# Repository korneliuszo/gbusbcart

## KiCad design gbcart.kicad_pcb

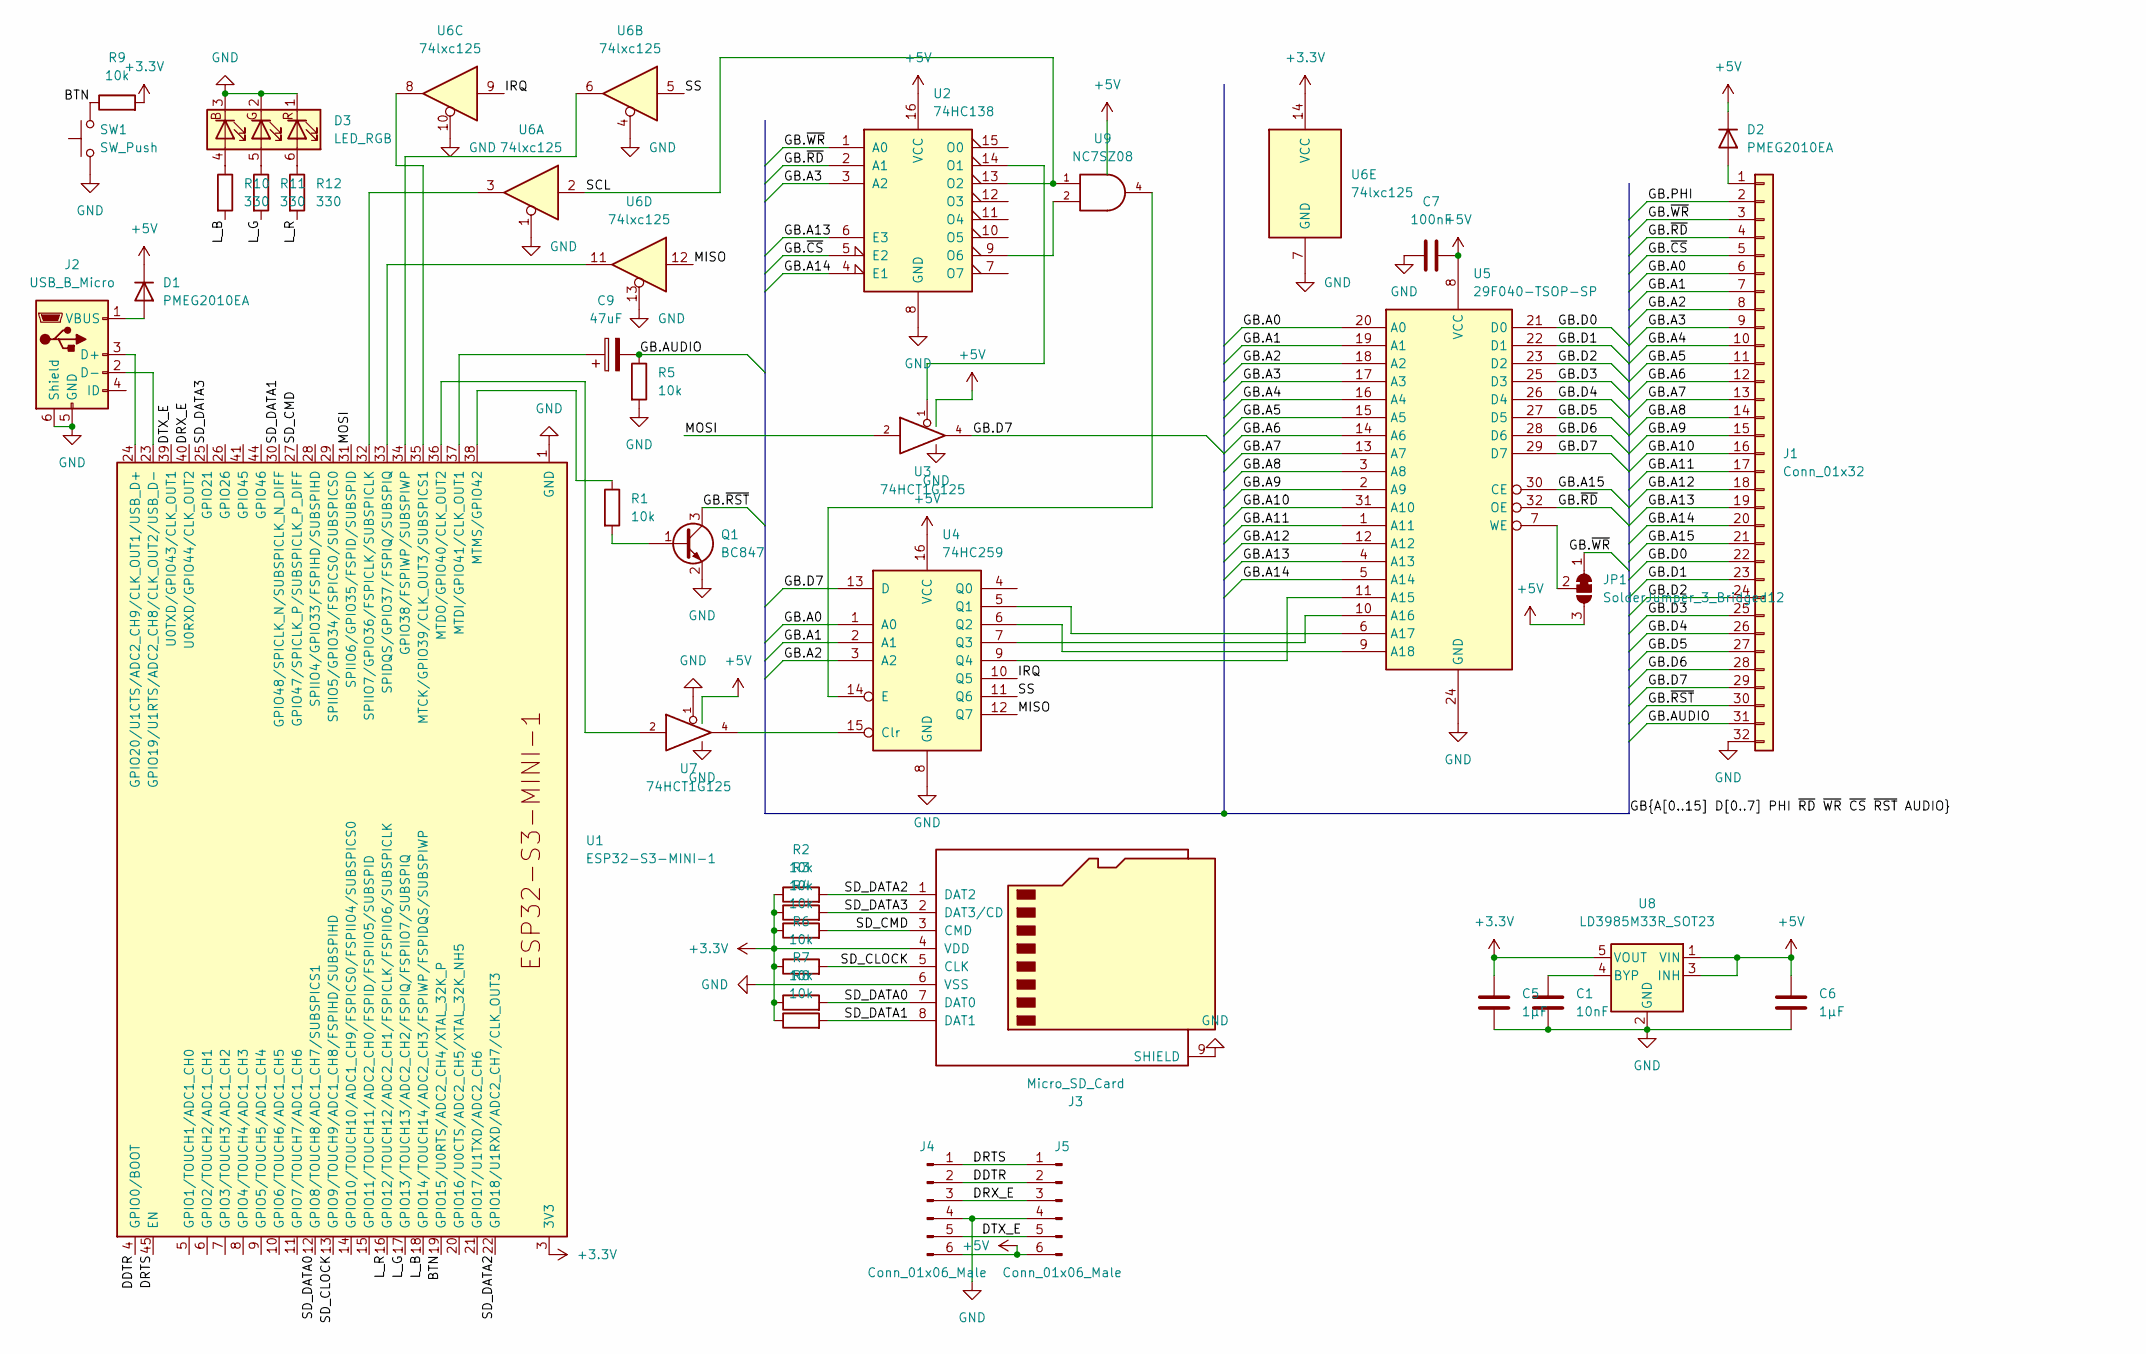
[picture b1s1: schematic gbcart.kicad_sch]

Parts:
C1: 10nF; C_0805_2012Metric_Pad1.18x1.45mm_HandSolder
C5, C6: 1µF; C_0805_2012Metric_Pad1.18x1.45mm_HandSolder
C7: 100nF; C_0805_2012Metric_Pad1.18x1.45mm_HandSolder
C9: 47uF; CP_EIA-7343-31_Kemet-D
D1, D2: PMEG2010EA; D_SOD-323
D3: LED_RGB; LED_RGB_PLCC-6
J1: Conn_01x32; GameBoy_Cartridge_1x32_P1.50mm_Edge
J2: USB_B_Micro; USB_Micro-B_Amphenol_10103594-0001LF_Horizontal
J3: Micro_SD_Card; microSD_HC_Molex_47219-2001
J4: Conn_01x06_Male; PinHeader_2x03_P2.54mm_Vertical_SMD
J5: Conn_01x06_Male; PinHeader_2x03_P2.54mm_Vertical
JP1: SolderJumper_3_Bridged12; SolderJumper-3_P2.0mm_Open_TrianglePad1.0x1.5mm_NumberLabels
Q1: BC847; SOT-23
R1, R2, R3, R4, R5, R6, R7, R8, R9: 10k; R_0402_1005Metric_Pad0.72x0.64mm_HandSolder
R10, R11, R12: 330; R_0402_1005Metric_Pad0.72x0.64mm_HandSolder
SW1: SW_Push; SW_SPST_FSMSM
U1: ESP32-S3-MINI-1
U2: 74HC138; SO-16_3.9x9.9mm_P1.27mm
U3, U7: 74HCT1G125; SOT-353_SC-70-5_Handsoldering
U4: 74HC259; SO-16_3.9x9.9mm_P1.27mm
U5: 29F040-TSOP-SP; TSOP-I-32_18.4x8mm_P0.5mm
U6: 74lxc125; SO-14_3.9x8.65mm_P1.27mm
U8: LD3985M33R_SOT23; SOT-23-5
U9: NC7SZ08; SOT-353_SC-70-5_Handsoldering

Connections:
+3.3V: C5.1, J3.4 (VDD), R2.1, R3.1, R4.1, R6.1, R7.1, R8.1, R9.2, U1.3 (3V3), U6.14 (VCC), U8.5 (VOUT)
+5V: C6.1, C7.2, D1.1 (K), D2.1 (K), J4.6, J5.6, JP1.3 (B), U2.16 (VCC), U3.5 (VCC), U4.16 (VCC), U5.8 (VCC), U7.5 (VCC), U8.1 (VIN), U8.3 (INH), U9.5 (VCC)
/BTN: R9.1, SW1.2, U1.19 (GPIO15/U0RTS/ADC2_CH4/XTAL_32K_P)
/DDTR: J4.2, J5.2, U1.4 (GPIO0/BOOT)
/DRTS: J4.1, J5.1, U1.45 (EN)
/DRX_E: J4.3, J5.3, U1.40 (U0RXD/GPIO44/CLK_OUT2)
/DTX_E: J4.5, J5.5, U1.39 (U0TXD/GPIO43/CLK_OUT1)
/GB.A0: J1.6, U4.1 (A0), U5.20 (A0)
/GB.A1: J1.7, U4.2 (A1), U5.19 (A1)
/GB.A2: J1.8, U4.3 (A2), U5.18 (A2)
/GB.A3: J1.9, U2.3 (A2), U5.17 (A3)
/GB.A4: J1.10, U5.16 (A4)
/GB.A5: J1.11, U5.15 (A5)
/GB.A6: J1.12, U5.14 (A6)
/GB.A7: J1.13, U5.13 (A7)
/GB.A8: J1.14, U5.3 (A8)
/GB.A9: J1.15, U5.2 (A9)
/GB.A10: J1.16, U5.31 (A10)
/GB.A11: J1.17, U5.1 (A11)
/GB.A12: J1.18, U5.12 (A12)
/GB.A13: J1.19, U2.6 (E3), U5.4 (A13)
/GB.A14: J1.20, U2.4 (E1), U5.5 (A14)
/GB.A15: J1.21, U5.30 (CE)
/GB.AUDIO: C9.2, J1.31, R5.1
/GB.D0: J1.22, U5.21 (D0)
/GB.D1: J1.23, U5.22 (D1)
/GB.D2: J1.24, U5.23 (D2)
/GB.D3: J1.25, U5.25 (D3)
/GB.D4: J1.26, U5.26 (D4)
/GB.D5: J1.27, U5.27 (D5)
/GB.D6: J1.28, U5.28 (D6)
/GB.D7: J1.29, U3.4, U4.13 (D), U5.29 (D7)
/GB.PHI: J1.2
/GB.~CS: J1.5, U2.5 (E2)
/GB.~RD: J1.4, U2.2 (A1), U5.32 (OE)
/GB.~RST: J1.30, Q1.3 (C)
/GB.~WR: J1.3, JP1.1 (A), U2.1 (A0)
/IRQ: U4.10 (Q5), U6.9
/L_B: R10.2, U1.18 (GPIO14/TOUCH14/ADC2_CH3/FSPIWP/FSPIDQS/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)
/L_G: R11.2, U1.17 (GPIO13/TOUCH13/ADC2_CH2/FSPIQ/FSPIIO7/S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)
/L_R: R12.2, U1.16 (GPIO12/TOUCH12/ADC2_CH1/FSPICLK/FSPIIO6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)
/MISO: U4.12 (Q7), U6.12
/MOSI: U1.31 (SPIIO6/GPIO35/FSPID/SUBSPID), U3.2
/SCL: U2.13 (O2), U6.2, U9.1
/SD_CLOCK: J3.5 (CLK), R6.2, U1.13 (GPIO9/TOUCH9/ADC1_CH8/FSPIHD/SUBSPIHD)
/SD_CMD: J3.3 (CMD), R4.2, U1.27 (GPIO47/SPICLK_P/SUBSPICLK_P_DIFF)
/SD_DATA0: J3.7 (DAT0), R7.2, U1.12 (GPIO8/TOUCH8/ADC1_CH7/SUBSPICS1)
/SD_DATA1: J3.8 (DAT1), R8.2, U1.30 (GPIO48/SPICLK_N/SUBSPICLK_N_DIFF)
/SD_DATA2: J3.1 (DAT2), R2.2, U1.22 (GPIO18/U1RXD/ADC2_CH7/CLK_OUT3)
/SD_DATA3: J3.2 (DAT3/CD), R3.2, U1.25 (GPIO21)
/SS: U4.11 (Q6), U6.5
GND: C1.2, C5.2, C6.2, C7.1, D3.1 (RK), D3.2 (GK), D3.3 (BK), J1.32, J2.5 (GND), J2.6 (Shield), J3.6 (VSS), J3.9 (SHIELD), J4.4, J5.4, Q1.2 (E), R5.2, SW1.1, U1.1 (GND), U1.2 (GND), U1.42 (GND), U1.43 (GND), U1.46 (GND), U1.47 (GND), U1.48 (GND), U1.49 (GND), U1.50 (GND), U1.51 (GND), U1.52 (GND), U1.53 (GND), U1.54 (GND), U1.55 (GND), U1.56 (GND), U1.57 (GND), U1.58 (GND), U1.59 (GND), U1.60 (GND), U1.61 (GND), U1.62 (GND), U1.63 (GND), U1.64 (GND), U1.65 (GND), U2.8 (GND), U3.3 (GND), U4.8 (GND), U5.24 (GND), U6.1, U6.4, U6.7 (GND), U6.10, U6.13, U7.1, U7.3 (GND), U8.2 (GND), U9.3 (GND)
unnamed: C1.1, U8.4 (BYP)
unnamed: C9.1, U1.37 (MTDI/GPIO41/CLK_OUT1)
unnamed: D1.2 (A), J2.1 (VBUS)
unnamed: D2.2 (A), J1.1
unnamed: D3.4 (BA), R10.1
unnamed: D3.5 (GA), R11.1
unnamed: D3.6 (RA), R12.1
unnamed: J2.2 (D-), U1.23 (GPIO19/U1RTS/ADC2_CH8/CLK_OUT2/USB_D-)
unnamed: J2.3 (D+), U1.24 (GPIO20/U1CTS/ADC2_CH9/CLK_OUT1/USB_D+)
unnamed: JP1.2 (C), U5.7 (WE)
unnamed: Q1.1 (B), R1.2
unnamed: R1.1, U1.38 (MTMS/GPIO42)
unnamed: U1.32 (SPIIO7/GPIO36/FSPICLK/SUBSPICLK), U6.3
unnamed: U1.33 (SPIDQS/GPIO37/FSPIQ/SUBSPIQ), U6.11
unnamed: U1.34 (GPIO38/FSPIWP/SUBSPIWP), U6.6
unnamed: U1.35 (MTCK/GPIO39/CLK_OUT3/SUBSPICS1), U6.8
unnamed: U1.36 (MTDO/GPIO40/CLK_OUT2), U7.2
unnamed: U2.9 (O6), U9.2
unnamed: U2.14 (O1), U3.1
unnamed: U4.5 (Q1), U5.6 (A17)
unnamed: U4.6 (Q2), U5.9 (A18)
unnamed: U4.7 (Q3), U5.10 (A16)
unnamed: U4.9 (Q4), U5.11 (A15)
unnamed: U4.14 (E), U9.4
unnamed: U4.15 (Clr), U7.4

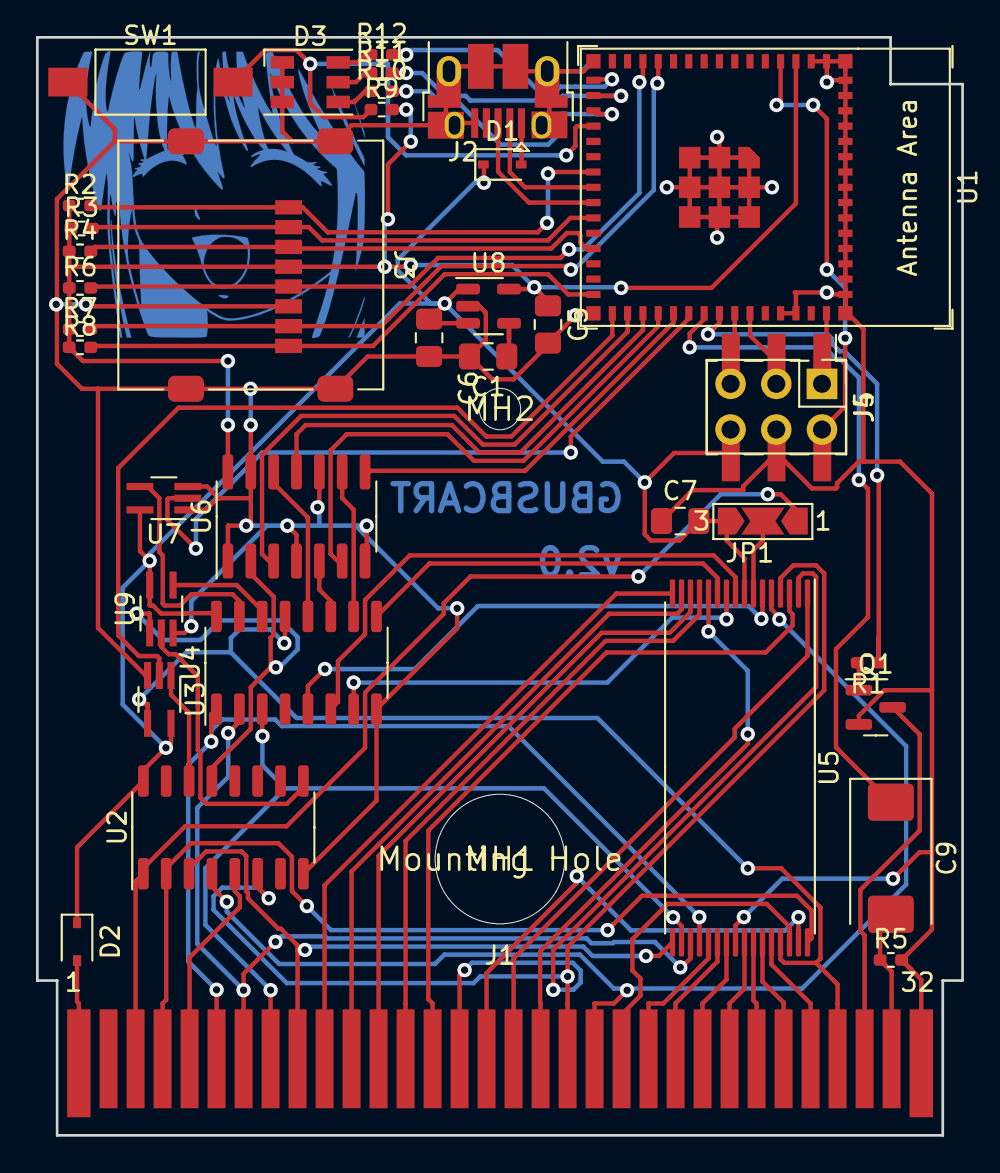
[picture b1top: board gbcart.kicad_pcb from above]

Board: 2 copper layers, 51.4 x 61.0 mm, 39 parts (0 on the bottom side), 76 nets.

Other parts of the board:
MH1: Mounting Hole; mountinghole1
MH2: Mountinghole2

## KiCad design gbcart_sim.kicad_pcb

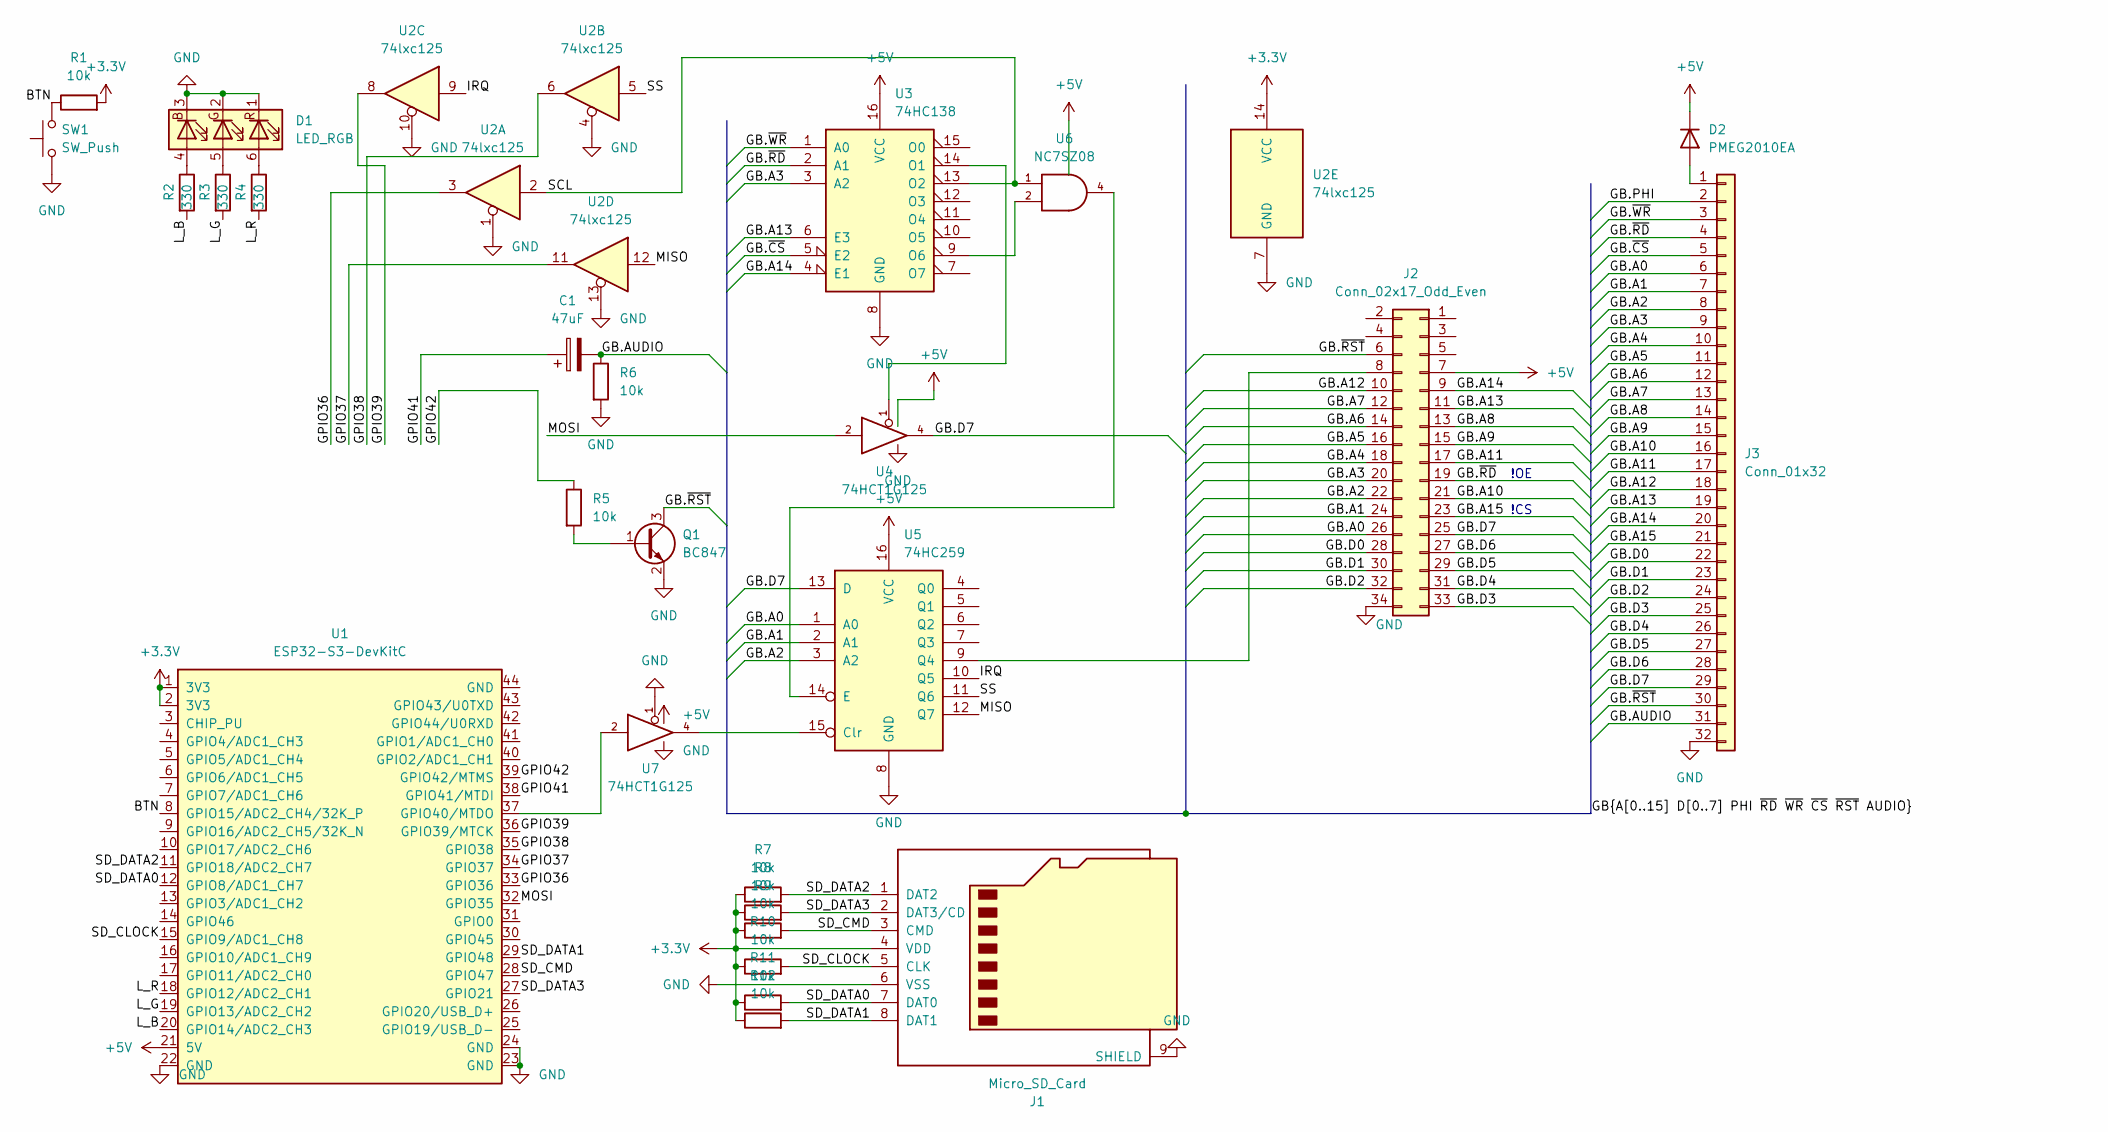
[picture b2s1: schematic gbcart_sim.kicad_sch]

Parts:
C1: 47uF; CP_EIA-7343-31_Kemet-D
D1: LED_RGB; LED_RGB_PLCC-6
D2: PMEG2010EA; D_SOD-323
J1: Micro_SD_Card; microSD_HC_Molex_47219-2001
J2: Conn_02x17_Odd_Even; IDC-Header_2x17_P2.54mm_Vertical
J3: Conn_01x32; IDC-Header_2x17_P2.54mm_Vertical
Q1: BC847; SOT-23
R1, R5, R6, R7, R8, R9, R10, R11, R12: 10k; R_0402_1005Metric_Pad0.72x0.64mm_HandSolder
R2, R3, R4: 330; R_0402_1005Metric_Pad0.72x0.64mm_HandSolder
SW1: SW_Push; SW_SPST_FSMSM
U1: ESP32-S3-DevKitC
U2: 74lxc125; SO-14_3.9x8.65mm_P1.27mm
U3: 74HC138; SO-16_3.9x9.9mm_P1.27mm
U4, U7: 74HCT1G125; SOT-353_SC-70-5_Handsoldering
U5: 74HC259; SO-16_3.9x9.9mm_P1.27mm
U6: NC7SZ08; SOT-353_SC-70-5_Handsoldering

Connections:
+3.3V: J1.4 (VDD), R1.2, R7.1, R8.1, R9.1, R10.1, R11.1, R12.1, U1.1 (3V3), U1.2 (3V3), U2.14 (VCC)
+5V: D2.1 (K), J2.7, U1.21 (5V), U3.16 (VCC), U4.5 (VCC), U5.16 (VCC), U6.5 (VCC), U7.5 (VCC)
/BTN: R1.1, SW1.2, U1.8 (GPIO15/ADC2_CH4/32K_P)
/GB.A0: J2.26, J3.6, U5.1 (A0)
/GB.A1: J2.24, J3.7, U5.2 (A1)
/GB.A2: J2.22, J3.8, U5.3 (A2)
/GB.A3: J2.20, J3.9, U3.3 (A2)
/GB.A4: J2.18, J3.10
/GB.A5: J2.16, J3.11
/GB.A6: J2.14, J3.12
/GB.A7: J2.12, J3.13
/GB.A8: J2.13, J3.14
/GB.A9: J2.15, J3.15
/GB.A10: J2.21, J3.16
/GB.A11: J2.17, J3.17
/GB.A12: J2.10, J3.18
/GB.A13: J2.11, J3.19, U3.6 (E3)
/GB.A14: J2.9, J3.20, U3.4 (E1)
/GB.A15: J2.23, J3.21
/GB.AUDIO: C1.2, J3.31, R6.1
/GB.D0: J2.28, J3.22
/GB.D1: J2.30, J3.23
/GB.D2: J2.32, J3.24
/GB.D3: J2.33, J3.25
/GB.D4: J2.31, J3.26
/GB.D5: J2.29, J3.27
/GB.D6: J2.27, J3.28
/GB.D7: J2.25, J3.29, U4.4, U5.13 (D)
/GB.PHI: J3.2
/GB.~CS: J3.5, U3.5 (E2)
/GB.~RD: J2.19, J3.4, U3.2 (A1)
/GB.~RST: J2.6, J3.30, Q1.3 (C)
/GB.~WR: J3.3, U3.1 (A0)
/GPIO36: U1.33 (GPIO36), U2.3
/GPIO37: U1.34 (GPIO37), U2.11
/GPIO38: U1.35 (GPIO38), U2.6
/GPIO39: U1.36 (GPIO39/MTCK), U2.8
/GPIO41: C1.1, U1.38 (GPIO41/MTDI)
/GPIO42: R5.1, U1.39 (GPIO42/MTMS)
/IRQ: U2.9, U5.10 (Q5)
/L_B: R2.2, U1.20 (GPIO14/ADC2_CH3)
/L_G: R3.2, U1.19 (GPIO13/ADC2_CH2)
/L_R: R4.2, U1.18 (GPIO12/ADC2_CH1)
/MISO: U2.12, U5.12 (Q7)
/MOSI: U1.32 (GPIO35), U4.2
/SCL: U2.2, U3.13 (O2), U6.1
/SD_CLOCK: J1.5 (CLK), R10.2, U1.15 (GPIO9/ADC1_CH8)
/SD_CMD: J1.3 (CMD), R9.2, U1.28 (GPIO47)
/SD_DATA0: J1.7 (DAT0), R11.2, U1.12 (GPIO8/ADC1_CH7)
/SD_DATA1: J1.8 (DAT1), R12.2, U1.29 (GPIO48)
/SD_DATA2: J1.1 (DAT2), R7.2, U1.11 (GPIO18/ADC2_CH7)
/SD_DATA3: J1.2 (DAT3/CD), R8.2, U1.27 (GPIO21)
/SS: U2.5, U5.11 (Q6)
GND: D1.1 (RK), D1.2 (GK), D1.3 (BK), J1.6 (VSS), J1.9 (SHIELD), J2.34, J3.32, Q1.2 (E), R6.2, SW1.1, U1.22 (GND), U1.23 (GND), U1.24 (GND), U2.1, U2.4, U2.7 (GND), U2.10, U2.13, U3.8 (GND), U4.3 (GND), U5.8 (GND), U6.3 (GND), U7.1, U7.3 (GND)
unnamed: D1.4 (BA), R2.1
unnamed: D1.5 (GA), R3.1
unnamed: D1.6 (RA), R4.1
unnamed: D2.2 (A), J3.1
unnamed: J2.8, U5.9 (Q4)
unnamed: Q1.1 (B), R5.2
unnamed: U1.37 (GPIO40/MTDO), U7.2
unnamed: U3.9 (O6), U6.2
unnamed: U3.14 (O1), U4.1
unnamed: U5.14 (E), U6.4
unnamed: U5.15 (Clr), U7.4

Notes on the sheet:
!OE
!CS

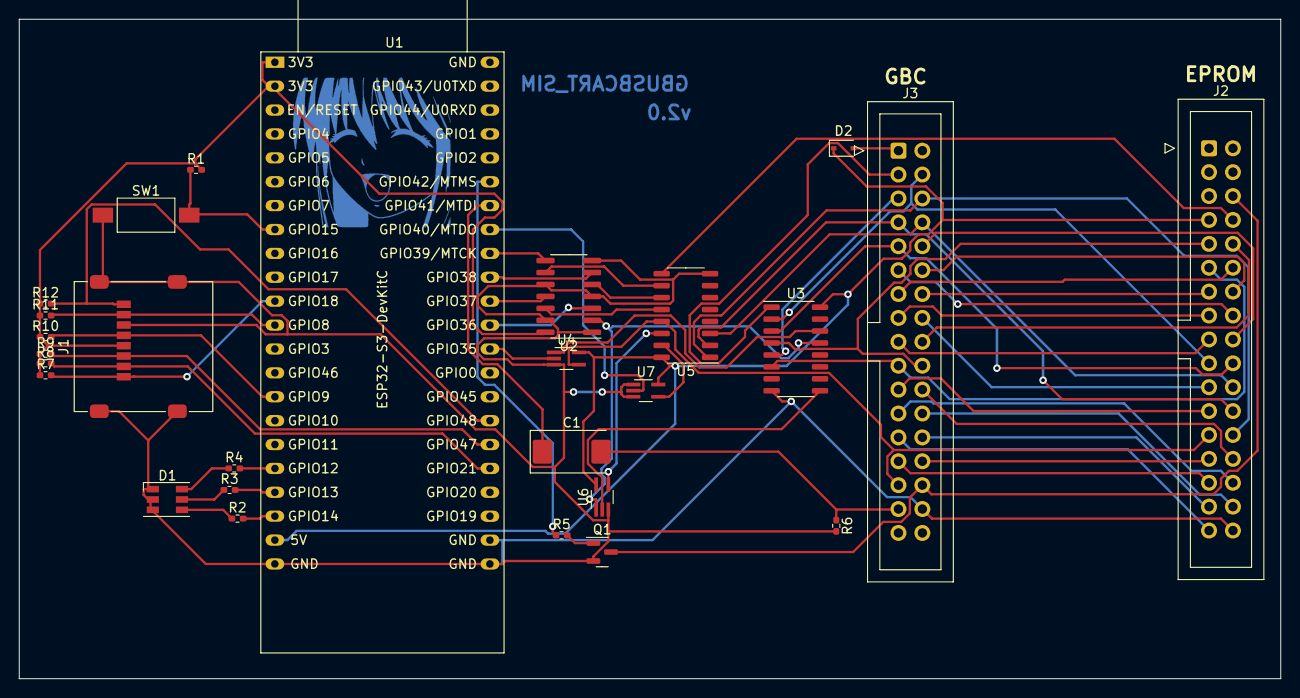
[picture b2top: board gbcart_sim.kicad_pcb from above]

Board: 2 copper layers, 134.1 x 70.1 mm, 27 parts (0 on the bottom side), 64 nets.

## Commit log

2023-01-10 Add generated files
2023-01-10 Add LICENCE
2023-01-10 DEV revision
2023-01-10 Add forgotten connection to A18
2023-01-11 Add LED and switch
2023-01-11 Mark proper 74 family
2023-02-04 choose diferent mcu
2023-02-05 Move connections to avalible on esp32-s3-DevkitC
2023-02-05 Move reset to seperate IO pin
2023-02-05 Add SIM board
2023-02-25 Move connector + add silkscren names
2023-02-26 Fix board
2023-02-26 Generate production files
